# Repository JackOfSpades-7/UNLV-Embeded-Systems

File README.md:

# UNLV-Embeded-Systems
Class projects for CPE 301 - Embedded Systems from UNLV Spring '24

Student author: Johnathan Widney

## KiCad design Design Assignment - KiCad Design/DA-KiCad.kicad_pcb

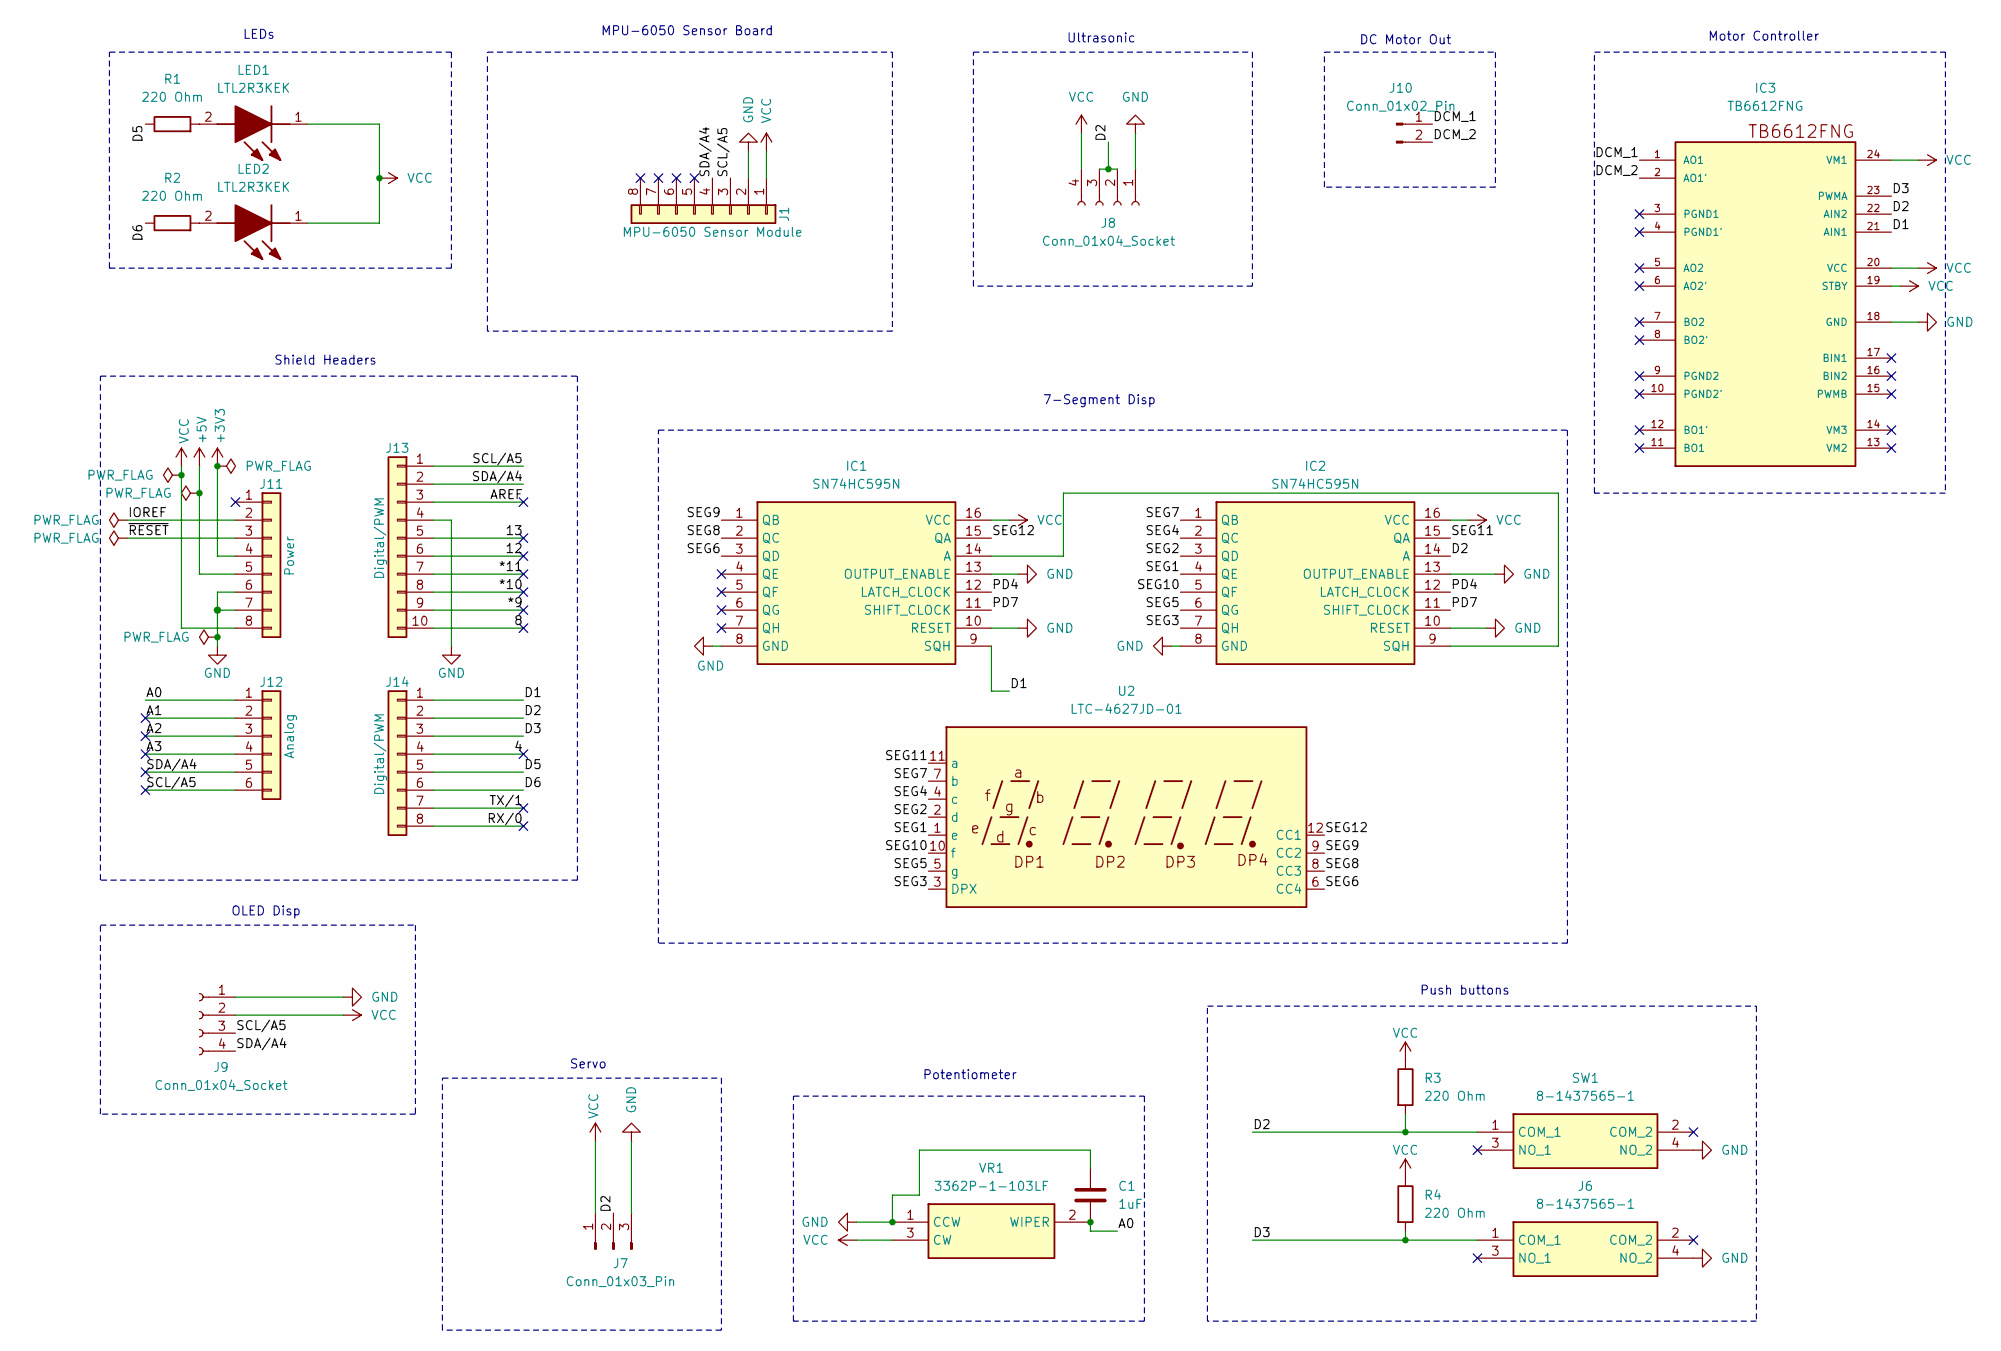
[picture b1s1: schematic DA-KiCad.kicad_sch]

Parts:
C1: 1uF; C_1210_3225Metric_Pad1.33x2.70mm_HandSolder
IC1, IC2: SN74HC595N; SOP65P640X120-16N; Mouser Part Number 863-MC74HC595ADTG
IC3: TB6612FNG; SSOP24
J1: MPU-6050 Sensor Module; PinSocket_1x08_P2.54mm_Vertical
J6: 8-1437565-1; 814375651; Mouser Part Number 506-8-1437565-1
J7: Conn_01x03_Pin; PinHeader_1x03_P2.54mm_Vertical
J8, J9: Conn_01x04_Socket; PinSocket_1x04_P2.54mm_Vertical
J10: Conn_01x02_Pin; PinHeader_1x02_P2.54mm_Vertical
J11: Power; PinSocket_1x08_P2.54mm_Vertical
J12: Analog; PinSocket_1x06_P2.54mm_Vertical
J13: Digital/PWM; PinSocket_1x10_P2.54mm_Vertical
J14: Digital/PWM; PinSocket_1x08_P2.54mm_Vertical
LED1, LED2: LTL2R3KEK; LED_Cree-PLCC4_3.2x2.8mm_CCW; Mouser Part Number 859-LTL2R3KEK
R1, R2, R3, R4: 220 Ohm; R_Axial_DIN0207_L6.3mm_D2.5mm_P10.16mm_Horizontal
SW1: 8-1437565-1; 814375651; Mouser Part Number 506-8-1437565-1
U2: LTC-4627JD-01; CA56-12SRWA
VR1: 3362P-1-103LF; 3362P_1; Mouser Part Number 652-3362P-1-103LF

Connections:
+3V3: J11.4
+5V: J11.5
/4: J14.4
/8: J13.10
/12: J13.6
/13: J13.5
/*9: J13.9
/*10: J13.8
/*11: J13.7
/A0: C1.2, J12.1, VR1.2 (WIPER)
/A1: J12.2
/A2: J12.3
/A3: J12.4
/AREF: J13.3
/D1: IC1.9 (SQH), IC3.21 (AIN1), J14.1
/D2: IC2.14 (A), IC3.22 (AIN2), J7.2, J8.2, J8.3, J14.2, R3.2, SW1.1 (COM_1)
/D3: IC3.23 (PWMA), J6.1 (COM_1), J14.3, R4.2
/D5: J14.5, R1.1
/D6: J14.6, R2.1
/DCM_1: IC3.1 (AO1), J10.1
/DCM_2: IC3.2 (AO1'), J10.2
/IOREF: J11.2
/PD4: IC1.12 (LATCH_CLOCK), IC2.12 (LATCH_CLOCK)
/PD7: IC1.11 (SHIFT_CLOCK), IC2.11 (SHIFT_CLOCK)
/RX/0: J14.8
/SCL/A5: J1.3, J9.3, J12.6, J13.1
/SDA/A4: J1.4, J9.4, J12.5, J13.2
/SEG1: IC2.4 (QE), U2.1 (e)
/SEG2: IC2.3 (QD), U2.2 (d)
/SEG3: IC2.7 (QH), U2.3 (DPX)
/SEG4: IC2.2 (QC), U2.4 (c)
/SEG5: IC2.6 (QG), U2.5 (g)
/SEG6: IC1.3 (QD), U2.6 (CC4)
/SEG7: IC2.1 (QB), U2.7 (b)
/SEG8: IC1.2 (QC), U2.8 (CC3)
/SEG9: IC1.1 (QB), U2.9 (CC2)
/SEG10: IC2.5 (QF), U2.10 (f)
/SEG11: IC2.15 (QA), U2.11 (a)
/SEG12: IC1.15 (QA), U2.12 (CC1)
/TX/1: J14.7
/~RESET: J11.3
GND: C1.1, IC1.8 (GND), IC1.10 (RESET), IC1.13 (OUTPUT_ENABLE), IC2.8 (GND), IC2.10 (RESET), IC2.13 (OUTPUT_ENABLE), IC3.18 (GND), J1.2, J6.4 (NO_2), J7.3, J8.1, J9.1, J11.6, J11.7, J13.4, SW1.4 (NO_2), VR1.1 (CCW)
unnamed: IC1.14 (A), IC2.9 (SQH)
unnamed: LED1.2 (A), R1.2
unnamed: LED2.2 (A), R2.2
VCC: IC1.16 (VCC), IC2.16 (VCC), IC3.19 (STBY), IC3.20 (VCC), IC3.24 (VM1), J1.1, J7.1, J8.4, J9.2, J11.8, LED1.1 (K), LED2.1 (K), R3.1, R4.1, VR1.3 (CW)

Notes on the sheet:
7-Segment Disp
Servo
Push buttons
DC Motor Out
MPU-6050 Sensor Board
Motor Controller
Shield Headers
OLED Disp
Potentiometer
LEDs
Ultrasonic

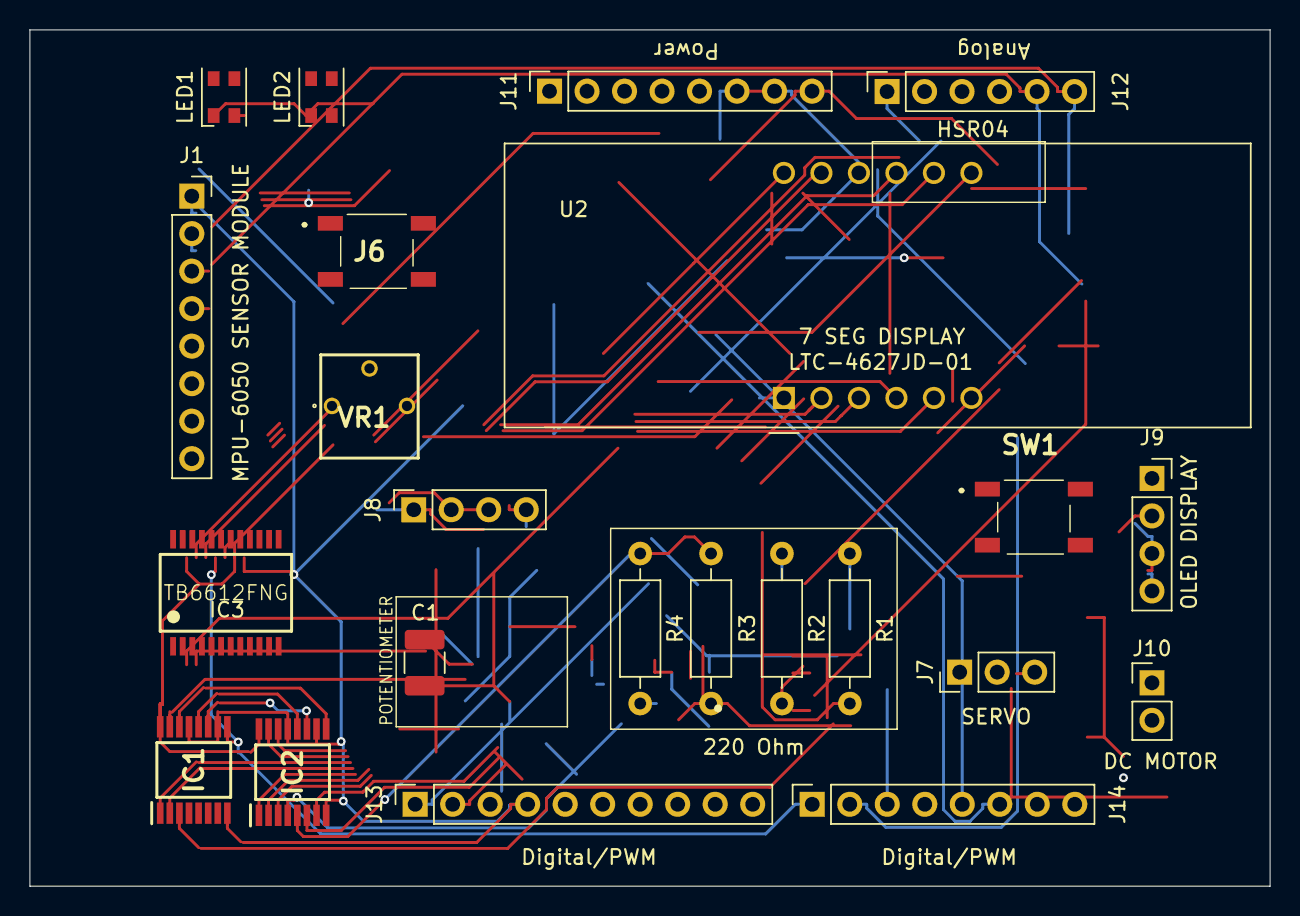
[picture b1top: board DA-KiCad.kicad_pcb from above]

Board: 2 copper layers, 84.0 x 58.0 mm, 23 parts (0 on the bottom side), 29 nets.

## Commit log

2024-02-26 Create Design Assignment 1 .asm
    Assembly code for design assignment 1
2024-02-26 Add files via upload
    Design assignment 1 report
2024-03-10 Create DA-2 Task 1-2 C code
2024-03-10 Create DA-2 Task 3 C code
2024-03-11 Create DA-2 Task 1-2 ASM code
2024-03-11 Create DA-2 Task 3 ASM code
2024-03-11 Add files via upload
    DA full report details
2024-04-14 Create DA-4 C code
2024-04-14 Update DA-4 C code
2024-04-22 Create DA5-C-code
2024-05-09 Create DA-6 Code Comprehensive (Tasks 1-4)
2024-05-10 Create KiCad DA
2024-05-10 Rename KiCad DA to KiCad DA - Readme File
2024-05-10 Rename KiCad DA - Readme File to ### KiCad DA - Readme File ###
